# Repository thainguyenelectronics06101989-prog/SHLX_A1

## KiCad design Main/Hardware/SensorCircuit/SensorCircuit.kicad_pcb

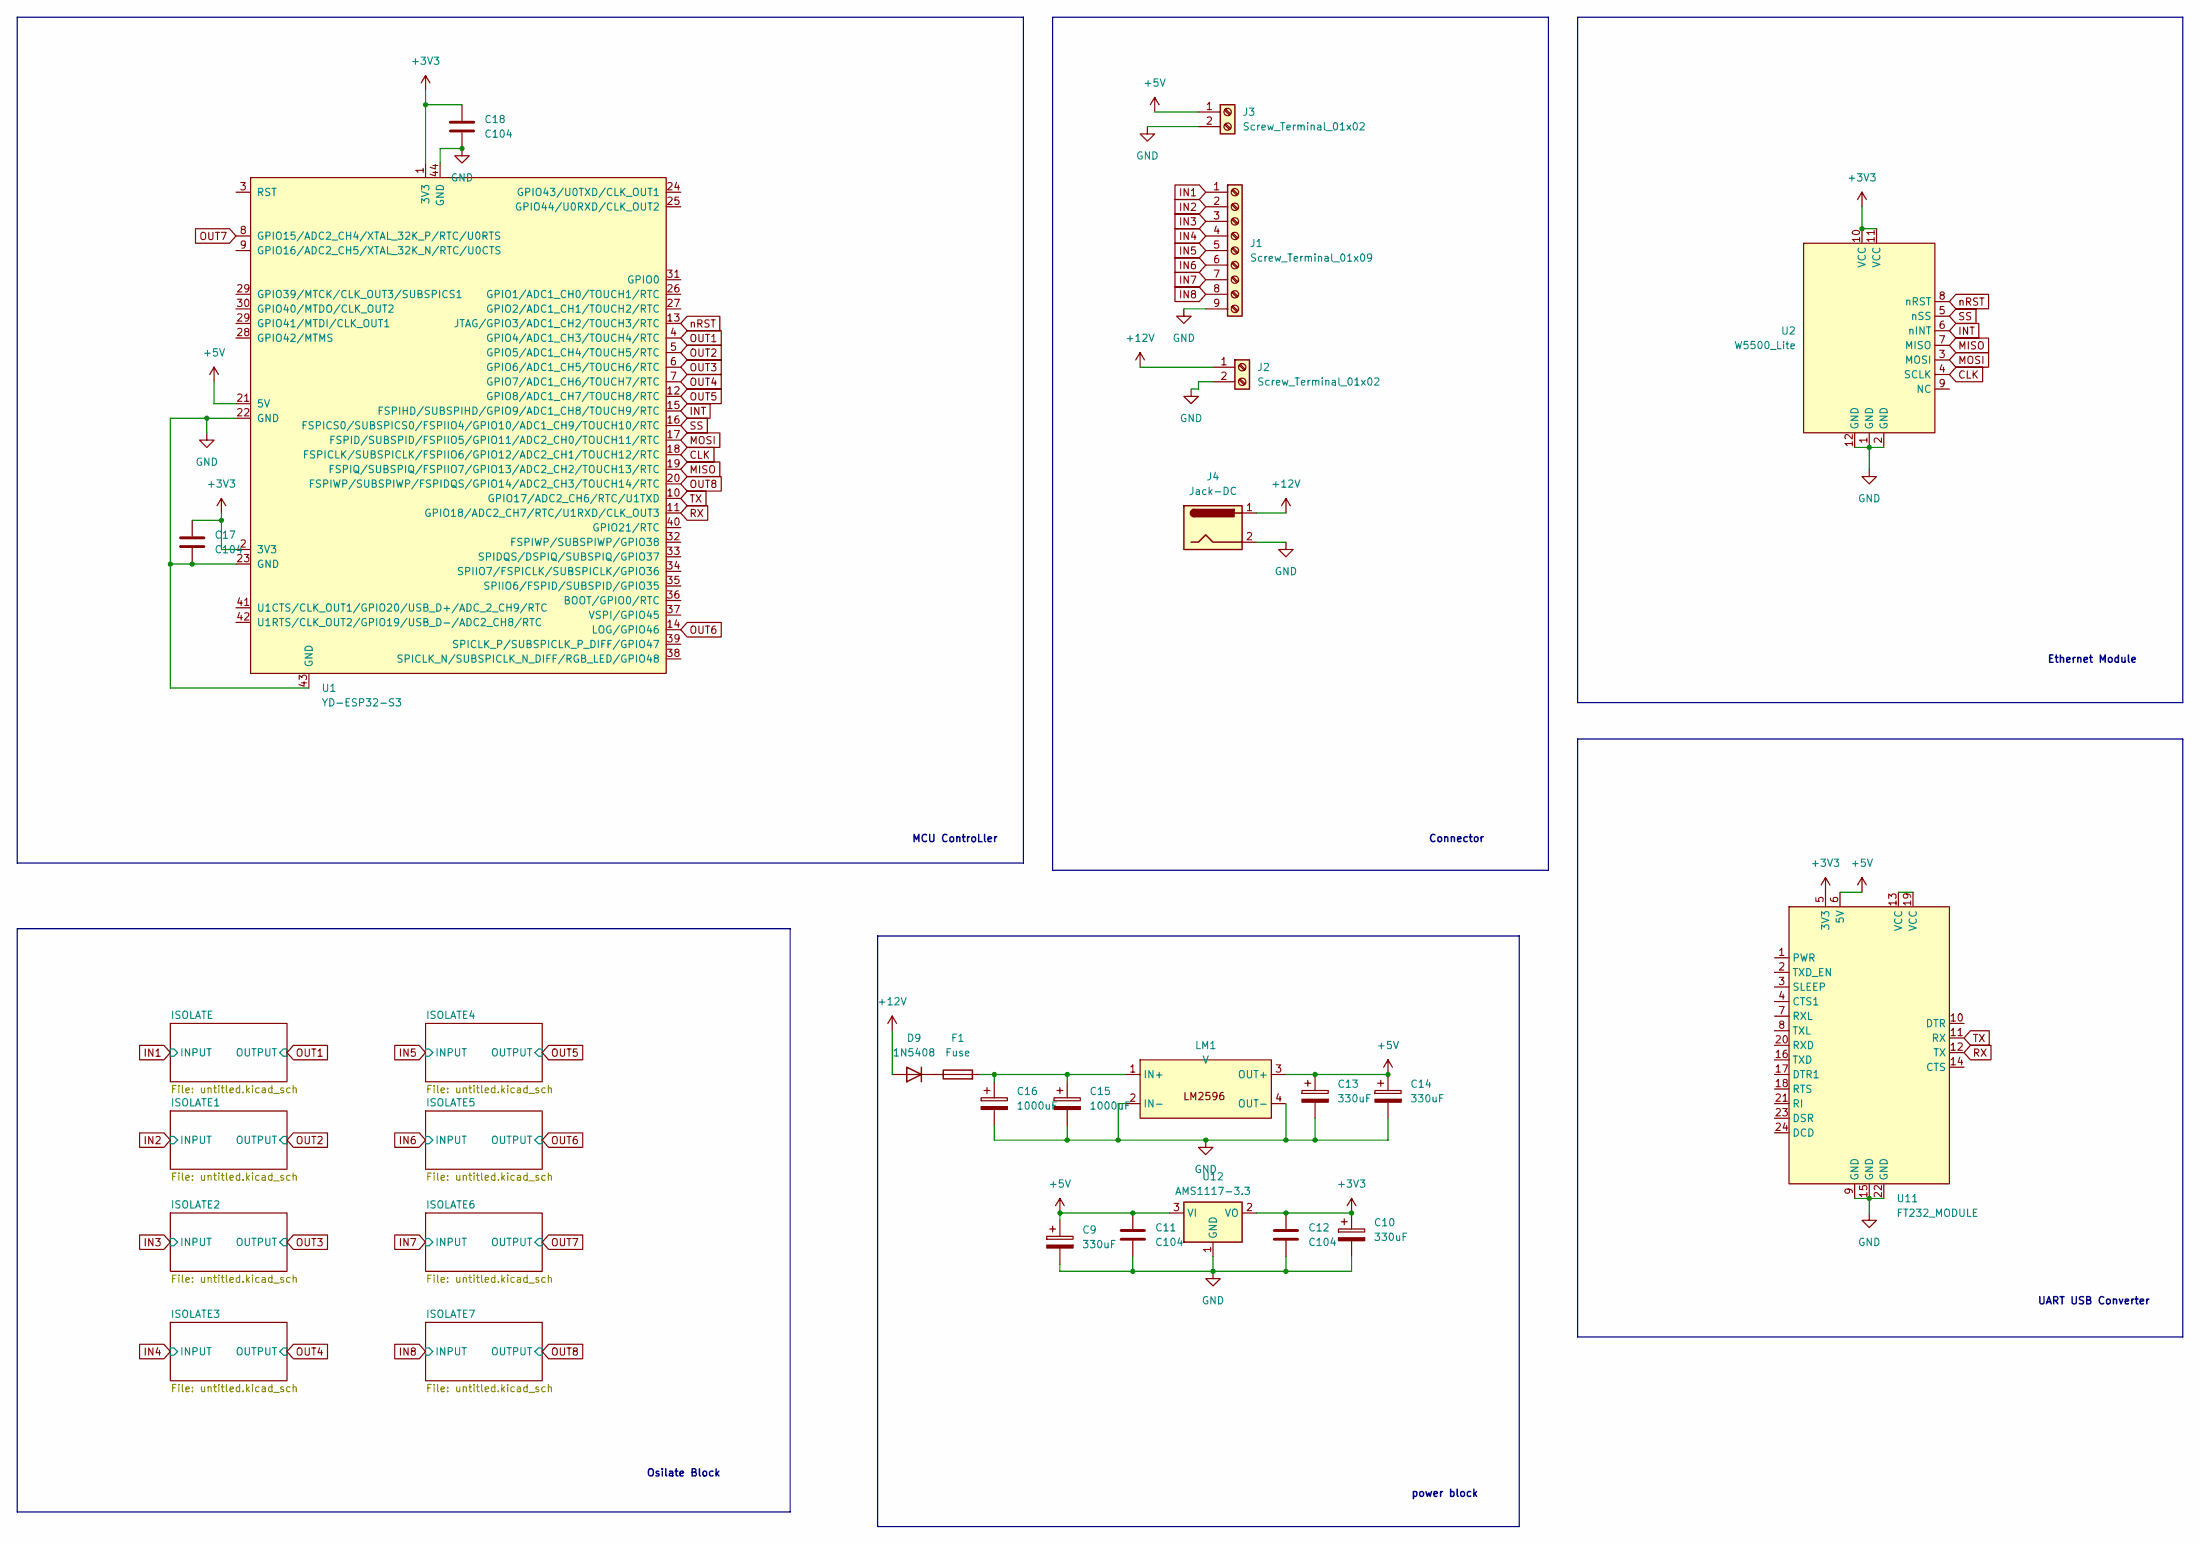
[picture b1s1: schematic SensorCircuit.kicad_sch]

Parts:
C9, C10, C13, C14: 330uF; C_Radial_D8.0mm_H7.0mm_P3.50mm
C11, C12, C17, C18: C104; C_Disc_D5.0mm_W2.5mm_P5.00mm
C15, C16: 1000uF; C_Radial_D10.0mm_H12.5mm_P5.00mm
D9: 1N5408; D_DO-201AD_P15.24mm_Horizontal
F1: Fuse; Fuseholder_Clip-5x20mm_Schurter_OG_Lateral_P15.00x5.00mm_D1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
J1: Screw_Terminal_01x09; TerminalBlock_Phoenix_MKDS-1,5-9-5.08_1x09_P5.08mm_Horizont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
J2, J3: Screw_Terminal_01x02; TerminalBlock_Phoenix_MKDS-1,5-2-5.08_1x02_P5.08mm_Horizont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
J4: Jack-DC; BarrelJack_GCT_DCJ200-10-A_Horizontal
LM1: V; LM2596_Module
U1: YD-ESP32-S3
U2: W5500_Lite; W5500_Lite_module
U11: FT232_MODULE; FT232_Module
U12: AMS1117-3.3; SOT-223-3_TabPin2

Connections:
+3V3: C10.1, C12.1, C17.1, C18.1, U1.1 (3V3), U1.2 (3V3), U2.10 (VCC), U2.11 (VCC), U11.5 (3V3), U12.2 (VO); also elsewhere on the board
+5V: C9.1, C11.1, C13.1, C14.1, J3.1, LM1.3 (OUT+), U1.21 (5V), U11.6 (5V), U12.3 (VI)
+12V: D9.2 (A), J2.1, J4.1; also elsewhere on the board
CLK: U1.18 (FSPICLK/SUBSPICLK/FSPIIO6/GPIO12/ADC2_C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), U2.4 (SCLK)
GND: C9.2, C10.2, C11.2, C12.2, C13.2, C14.2, C15.2, C16.2, C17.2, C18.2, J1.9, J2.2, J3.2, J4.2, LM1.2 (IN-), LM1.4 (OUT-), U1.22 (GND), U1.23 (GND), U1.43 (GND), U1.44 (GND), U2.1 (GND), U2.2 (GND), U2.12 (GND), U11.9 (GND), U11.15 (GND), U11.22 (GND), U12.1 (GND); also elsewhere on the board
IN1: J1.1; also elsewhere on the board
IN2: J1.2; also elsewhere on the board
IN3: J1.3; also elsewhere on the board
IN4: J1.4; also elsewhere on the board
IN5: J1.5; also elsewhere on the board
IN6: J1.6; also elsewhere on the board
IN7: J1.7; also elsewhere on the board
IN8: J1.8; also elsewhere on the board
INT: U1.15 (FSPIHD/SUBSPIHD/GPIO9/ADC1_CH8/TOUCH9/R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), U2.6 (nINT)
MISO: U1.19 (FSPIQ/SUBSPIQ/FSPIIO7/GPIO13/ADC2_CH2/T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), U2.7 (MISO)
MOSI: U1.17 (FSPID/SUBSPID/FSPIIO5/GPIO11/ADC2_CH0/T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), U2.3 (MOSI)
unnamed: D9.1 (K), F1.1
unnamed: C15.1, C16.1, F1.2, LM1.1 (IN+)
unnamed: U11.13 (VCC), U11.19 (VCC)
OUT1: U1.4 (GPIO4/ADC1_CH3/TOUCH4/RTC); also elsewhere on the board
OUT2: U1.5 (GPIO5/ADC1_CH4/TOUCH5/RTC); also elsewhere on the board
OUT3: U1.6 (GPIO6/ADC1_CH5/TOUCH6/RTC); also elsewhere on the board
OUT4: U1.7 (GPIO7/ADC1_CH6/TOUCH7/RTC); also elsewhere on the board
OUT5: U1.12 (GPIO8/ADC1_CH7/TOUCH8/RTC); also elsewhere on the board
OUT6: U1.14 (LOG/GPIO46); also elsewhere on the board
OUT7: U1.8 (GPIO15/ADC2_CH4/XTAL_32K_P/RTC/U0RTS); also elsewhere on the board
OUT8: U1.20 (FSPIWP/SUBSPIWP/FSPIDQS/GPIO14/ADC2_CH3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); also elsewhere on the board
RX: U1.11 (GPIO18/ADC2_CH7/RTC/U1RXD/CLK_OUT3), U11.12 (TX)
SS: U1.16 (FSPICS0/SUBSPICS0/FSPIIO4/GPIO10/ADC1_C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), U2.5 (nSS)
TX: U1.10 (GPIO17/ADC2_CH6/RTC/U1TXD), U11.11 (RX)
nRST: U1.13 (JTAG/GPIO3/ADC1_CH2/TOUCH3/RTC), U2.8 (nRST)

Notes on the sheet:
Ethernet Module
UART USB Converter
Osilate Block
Connector
MCU ControLler
power block

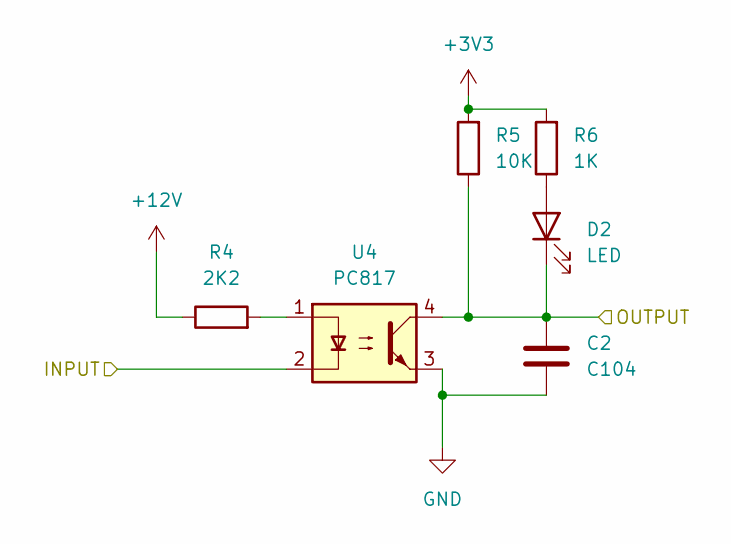
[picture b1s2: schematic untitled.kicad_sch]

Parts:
C2: C104; C_Disc_D5.0mm_W2.5mm_P5.00mm
D2: LED; LED_D3.0mm
R4: 2K2; R_Axial_DIN0207_L6.3mm_D2.5mm_P7.62mm_Horizontal
R5: 10K; R_Axial_DIN0207_L6.3mm_D2.5mm_P7.62mm_Horizontal
R6: 1K; R_Axial_DIN0207_L6.3mm_D2.5mm_P7.62mm_Horizontal
U4: PC817; DIP-4_W7.62mm

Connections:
+3V3: R5.2, R6.2; also elsewhere on the board
+12V: R4.1; also elsewhere on the board
GND: C2.2, U4.3; also elsewhere on the board
IN1: U4.2; also elsewhere on the board
unnamed: D2.2 (A), R6.1
unnamed: R4.2, U4.1
OUT1: C2.1, D2.1 (K), R5.1, U4.4; also elsewhere on the board

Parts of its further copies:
C1, C3, C4, C5, C6, C7, C8: C104; C_Disc_D5.0mm_W2.5mm_P5.00mm
D1, D3, D4, D5, D6, D7, D8: LED; LED_D3.0mm
R1, R7, R10, R13, R16, R19, R22: 2K2; R_Axial_DIN0207_L6.3mm_D2.5mm_P7.62mm_Horizontal
R2, R8, R11, R14, R17, R20, R23: 10K; R_Axial_DIN0207_L6.3mm_D2.5mm_P7.62mm_Horizontal
R3, R9, R12, R15, R18, R21, R24: 1K; R_Axial_DIN0207_L6.3mm_D2.5mm_P7.62mm_Horizontal
U3, U5, U6, U7, U8, U9, U10: PC817; DIP-4_W7.62mm

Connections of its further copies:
+3V3: R2.2, R3.2, R8.2, R9.2, R11.2, R12.2, R14.2, R15.2, R17.2, R18.2, R20.2, R21.2, R23.2, R24.2; also elsewhere on the board
+12V: R1.1, R7.1, R10.1, R13.1, R16.1, R19.1, R22.1; also elsewhere on the board
GND: C1.2, C3.2, C4.2, C5.2, C6.2, C7.2, C8.2, U3.3, U5.3, U6.3, U7.3, U8.3, U9.3, U10.3; also elsewhere on the board
IN2: U3.2; also elsewhere on the board
IN3: U5.2; also elsewhere on the board
IN4: U6.2; also elsewhere on the board
IN5: U7.2; also elsewhere on the board
IN6: U8.2; also elsewhere on the board
IN7: U9.2; also elsewhere on the board
IN8: U10.2; also elsewhere on the board
unnamed: D1.2 (A), R3.1
unnamed: D3.2 (A), R9.1
unnamed: D4.2 (A), R12.1
unnamed: D5.2 (A), R15.1
unnamed: D6.2 (A), R18.1
unnamed: D7.2 (A), R21.1
unnamed: D8.2 (A), R24.1
unnamed: R1.2, U3.1
unnamed: R7.2, U5.1
unnamed: R10.2, U6.1
unnamed: R13.2, U7.1
unnamed: R16.2, U8.1
unnamed: R19.2, U9.1
unnamed: R22.2, U10.1
OUT2: C1.1, D1.1 (K), R2.1, U3.4; also elsewhere on the board
OUT3: C3.1, D3.1 (K), R8.1, U5.4; also elsewhere on the board
OUT4: C4.1, D4.1 (K), R11.1, U6.4; also elsewhere on the board
OUT5: C5.1, D5.1 (K), R14.1, U7.4; also elsewhere on the board
OUT6: C6.1, D6.1 (K), R17.1, U8.4; also elsewhere on the board
OUT7: C7.1, D7.1 (K), R20.1, U9.4; also elsewhere on the board
OUT8: C8.1, D8.1 (K), R23.1, U10.4; also elsewhere on the board

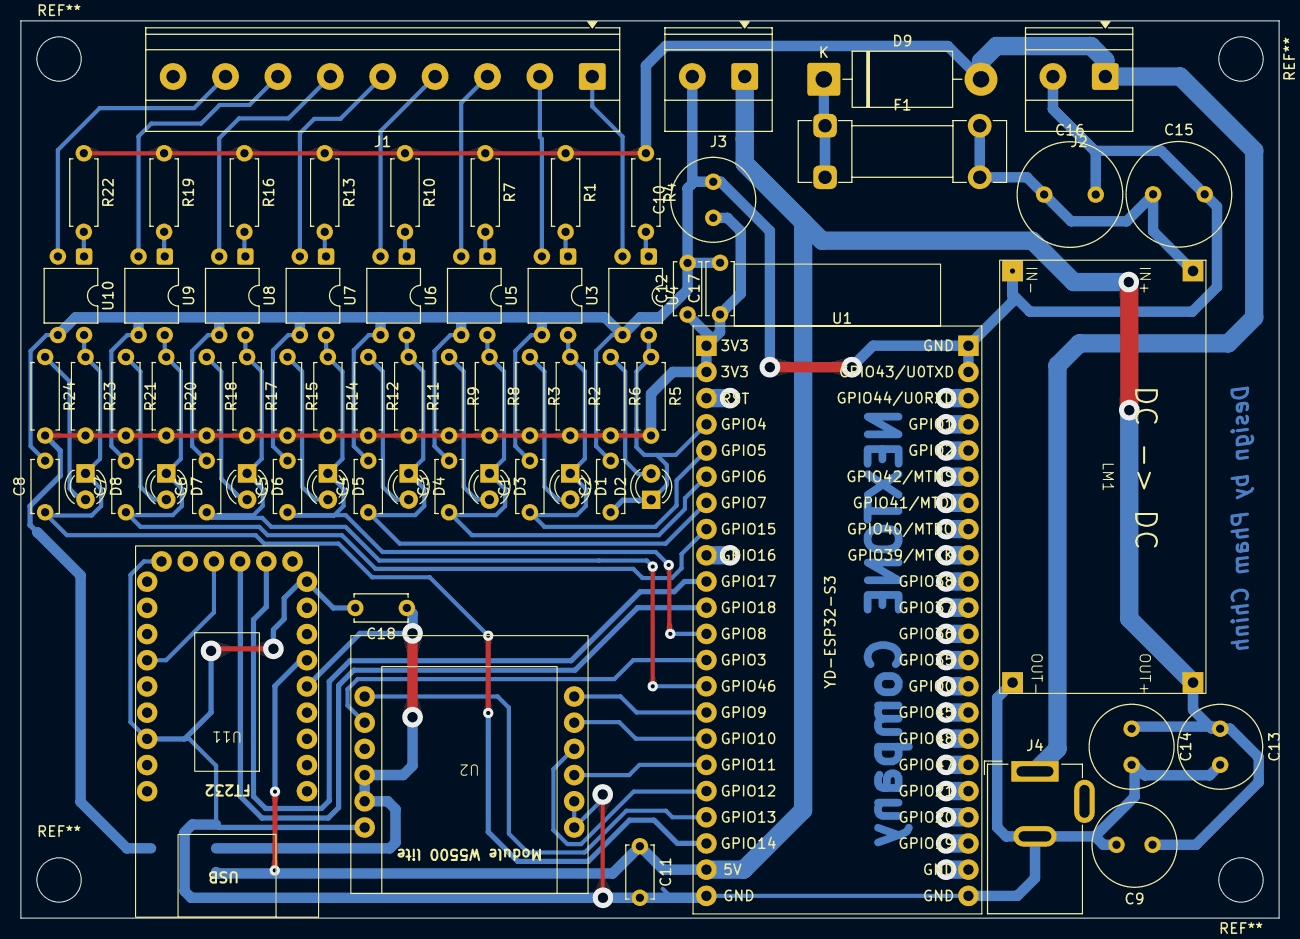
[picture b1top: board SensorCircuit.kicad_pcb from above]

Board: 2 copper layers, 122.0 x 87.0 mm, 69 parts (1 on the bottom side), 47 nets.

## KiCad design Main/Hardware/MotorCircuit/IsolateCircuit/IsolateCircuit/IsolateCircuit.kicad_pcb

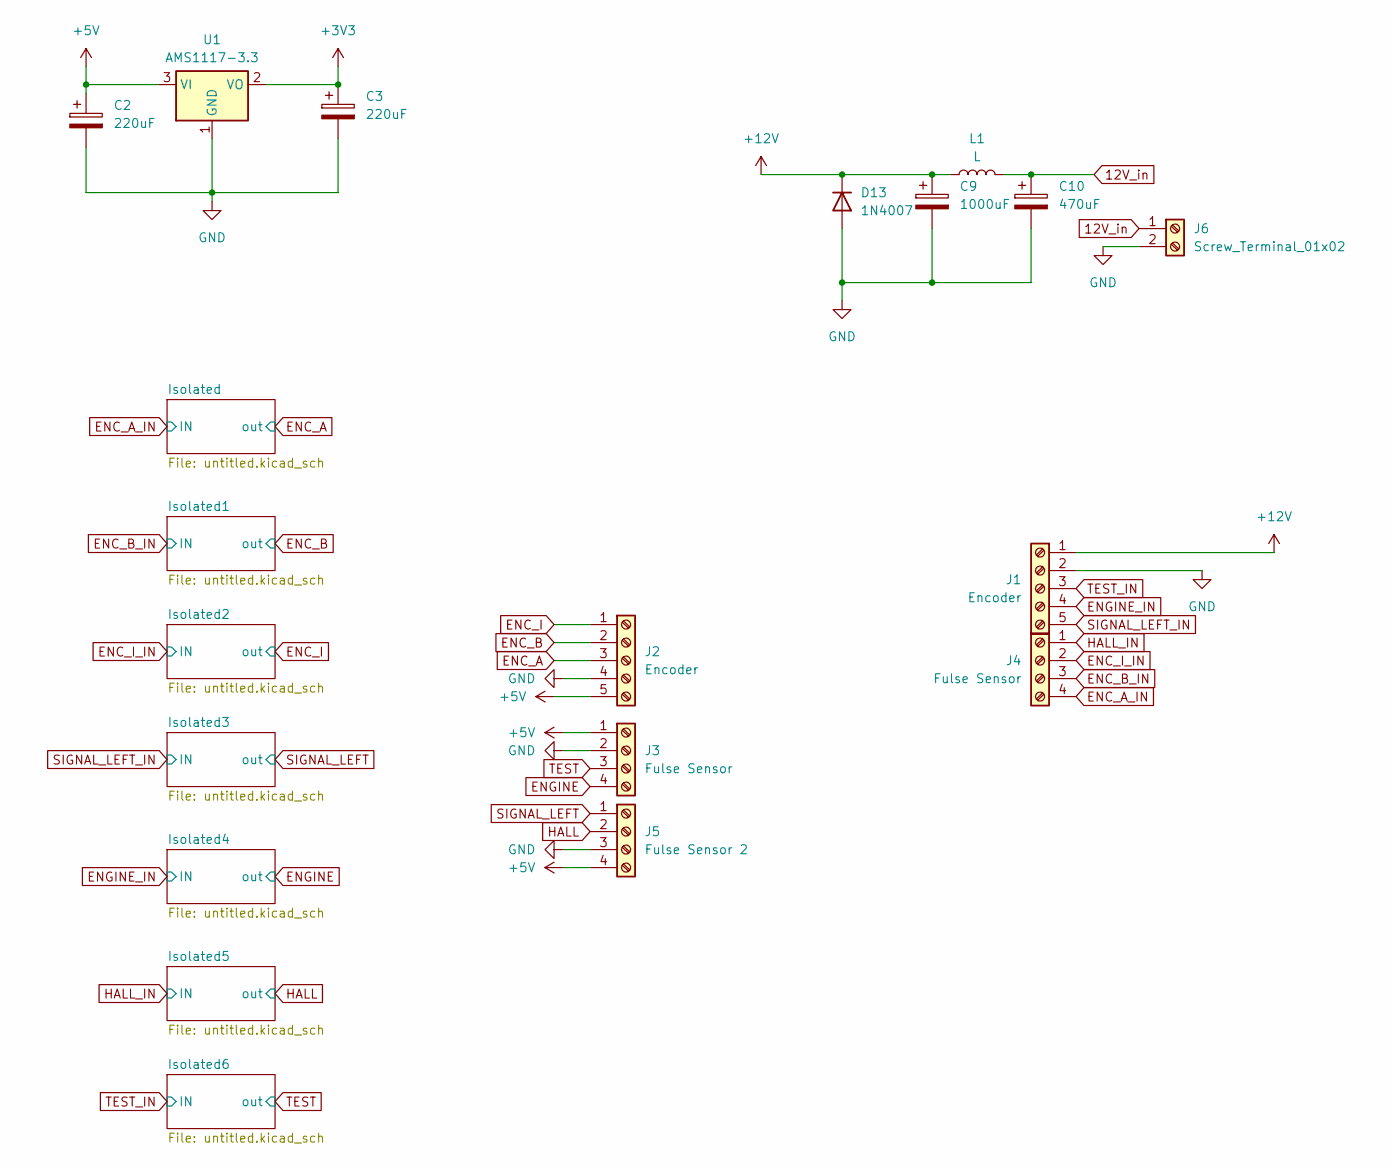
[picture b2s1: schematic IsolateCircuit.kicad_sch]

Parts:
C2, C3: 220uF; CP_Radial_D6.3mm_P2.50mm
C9: 1000uF; CP_Radial_D8.0mm_P2.50mm
C10: 470uF; CP_Radial_D8.0mm_P2.50mm
D13: 1N4007; D_DO-41_SOD81_P10.16mm_Horizontal
J1, J2: Encoder; TerminalBlock_Phoenix_MKDS-1,5-5-5.08_1x05_P5.08mm_Horizont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
J3, J4: Fulse Sensor; TerminalBlock_Phoenix_MKDS-1,5-4_1x04_P5.00mm_Horizontal
J5: Fulse Sensor 2; TerminalBlock_Phoenix_MKDS-1,5-4_1x04_P5.00mm_Horizontal
J6: Screw_Terminal_01x02; TerminalBlock_Phoenix_MKDS-1,5-2-5.08_1x02_P5.08mm_Horizont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
L1: L; L_Toroid_Vertical_L14.0mm_W5.6mm_P5.30mm_Bourns_5700
U1: AMS1117-3.3; SOT-223-3_TabPin2

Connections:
12V_in: C10.1, J6.1, L1.2
+3V3: C3.1, U1.2 (VO); also elsewhere on the board
+5V: C2.1, J2.5, J3.1, J5.4, U1.3 (VI)
+12V: C9.1, D13.1 (K), J1.1, L1.1; also elsewhere on the board
ENC_A: J2.3; also elsewhere on the board
ENC_A_IN: J4.4; also elsewhere on the board
ENC_B: J2.2; also elsewhere on the board
ENC_B_IN: J4.3; also elsewhere on the board
ENC_I: J2.1; also elsewhere on the board
ENC_I_IN: J4.2; also elsewhere on the board
ENGINE: J3.4; also elsewhere on the board
ENGINE_IN: J1.4; also elsewhere on the board
GND: C2.2, C3.2, C9.2, C10.2, D13.2 (A), J1.2, J2.4, J3.2, J5.3, J6.2, U1.1 (GND); also elsewhere on the board
HALL: J5.2; also elsewhere on the board
HALL_IN: J4.1; also elsewhere on the board
SIGNAL_LEFT: J5.1; also elsewhere on the board
SIGNAL_LEFT_IN: J1.5; also elsewhere on the board
TEST: J3.3; also elsewhere on the board
TEST_IN: J1.3; also elsewhere on the board

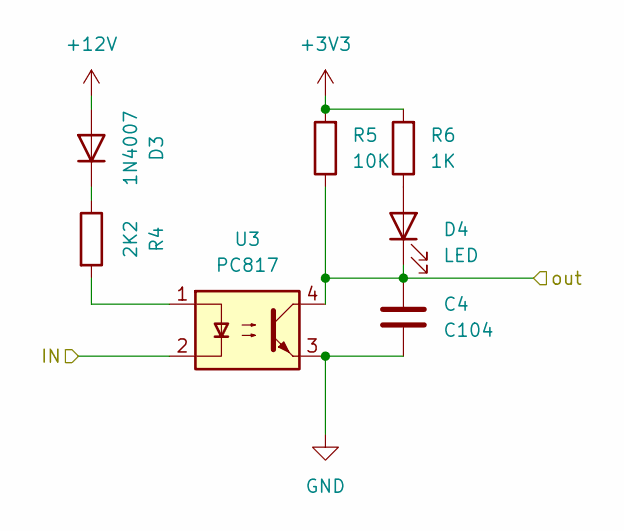
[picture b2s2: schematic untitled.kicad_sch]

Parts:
C4: C104; C_Disc_D5.1mm_W3.2mm_P5.00mm
D3: 1N4007; D_DO-41_SOD81_P10.16mm_Horizontal
D4: LED; LED_D3.0mm
R4: 2K2; R_Axial_DIN0207_L6.3mm_D2.5mm_P10.16mm_Horizontal
R5: 10K; R_Axial_DIN0207_L6.3mm_D2.5mm_P10.16mm_Horizontal
R6: 1K; R_Axial_DIN0207_L6.3mm_D2.5mm_P10.16mm_Horizontal
U3: PC817; DIP-4_W7.62mm

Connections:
+3V3: R5.2, R6.2; also elsewhere on the board
+12V: D3.2 (A); also elsewhere on the board
ENC_A: C4.1, D4.1 (K), R5.1, U3.4; also elsewhere on the board
ENC_A_IN: U3.2; also elsewhere on the board
GND: C4.2, U3.3; also elsewhere on the board
unnamed: D3.1 (K), R4.1
unnamed: D4.2 (A), R6.1
unnamed: R4.2, U3.1

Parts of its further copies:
C1, C5, C6, C7, C8, C11: C104; C_Disc_D5.1mm_W3.2mm_P5.00mm
D1, D5, D7, D9, D11, D14: 1N4007; D_DO-41_SOD81_P10.16mm_Horizontal
D2, D6, D8, D10, D12, D15: LED; LED_D3.0mm
R1, R7, R10, R13, R16, R19: 2K2; R_Axial_DIN0207_L6.3mm_D2.5mm_P10.16mm_Horizontal
R2, R8, R11, R14, R17, R20: 10K; R_Axial_DIN0207_L6.3mm_D2.5mm_P10.16mm_Horizontal
R3, R9, R12, R15, R18, R21: 1K; R_Axial_DIN0207_L6.3mm_D2.5mm_P10.16mm_Horizontal
U2, U4, U5, U6, U7, U8: PC817; DIP-4_W7.62mm

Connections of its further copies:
+3V3: R2.2, R3.2, R8.2, R9.2, R11.2, R12.2, R14.2, R15.2, R17.2, R18.2, R20.2, R21.2; also elsewhere on the board
+12V: D1.2 (A), D5.2 (A), D7.2 (A), D9.2 (A), D11.2 (A), D14.2 (A); also elsewhere on the board
ENC_B: C1.1, D2.1 (K), R2.1, U2.4; also elsewhere on the board
ENC_B_IN: U2.2; also elsewhere on the board
ENC_I: C5.1, D6.1 (K), R8.1, U4.4; also elsewhere on the board
ENC_I_IN: U4.2; also elsewhere on the board
ENGINE: C7.1, D10.1 (K), R14.1, U6.4; also elsewhere on the board
ENGINE_IN: U6.2; also elsewhere on the board
GND: C1.2, C5.2, C6.2, C7.2, C8.2, C11.2, U2.3, U4.3, U5.3, U6.3, U7.3, U8.3; also elsewhere on the board
HALL: C8.1, D12.1 (K), R17.1, U7.4; also elsewhere on the board
HALL_IN: U7.2; also elsewhere on the board
unnamed: D1.1 (K), R1.1
unnamed: D2.2 (A), R3.1
unnamed: D5.1 (K), R7.1
unnamed: D6.2 (A), R9.1
unnamed: D7.1 (K), R10.1
unnamed: D8.2 (A), R12.1
unnamed: D9.1 (K), R13.1
unnamed: D10.2 (A), R15.1
unnamed: D11.1 (K), R16.1
unnamed: D12.2 (A), R18.1
unnamed: D14.1 (K), R19.1
unnamed: D15.2 (A), R21.1
unnamed: R1.2, U2.1
unnamed: R7.2, U4.1
unnamed: R10.2, U5.1
unnamed: R13.2, U6.1
unnamed: R16.2, U7.1
unnamed: R19.2, U8.1
SIGNAL_LEFT: C6.1, D8.1 (K), R11.1, U5.4; also elsewhere on the board
SIGNAL_LEFT_IN: U5.2; also elsewhere on the board
TEST: C11.1, D15.1 (K), R20.1, U8.4; also elsewhere on the board
TEST_IN: U8.2; also elsewhere on the board

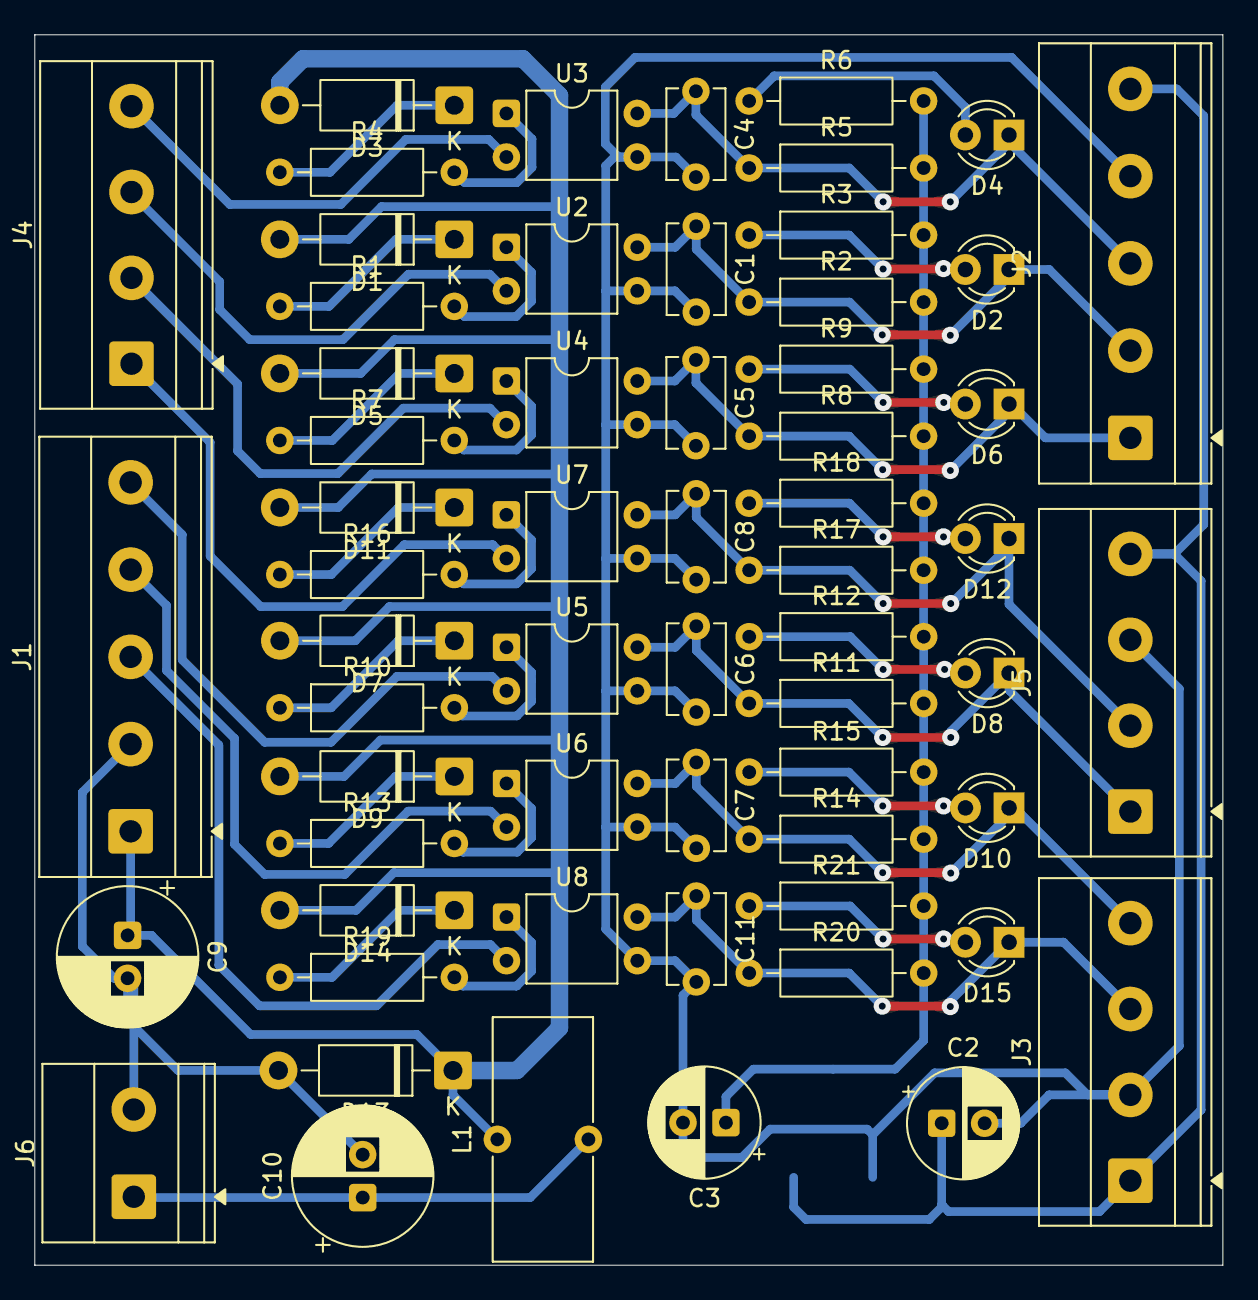
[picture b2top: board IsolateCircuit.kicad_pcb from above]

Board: 2 copper layers, 69.2 x 71.7 mm, 62 parts (1 on the bottom side), 40 nets.

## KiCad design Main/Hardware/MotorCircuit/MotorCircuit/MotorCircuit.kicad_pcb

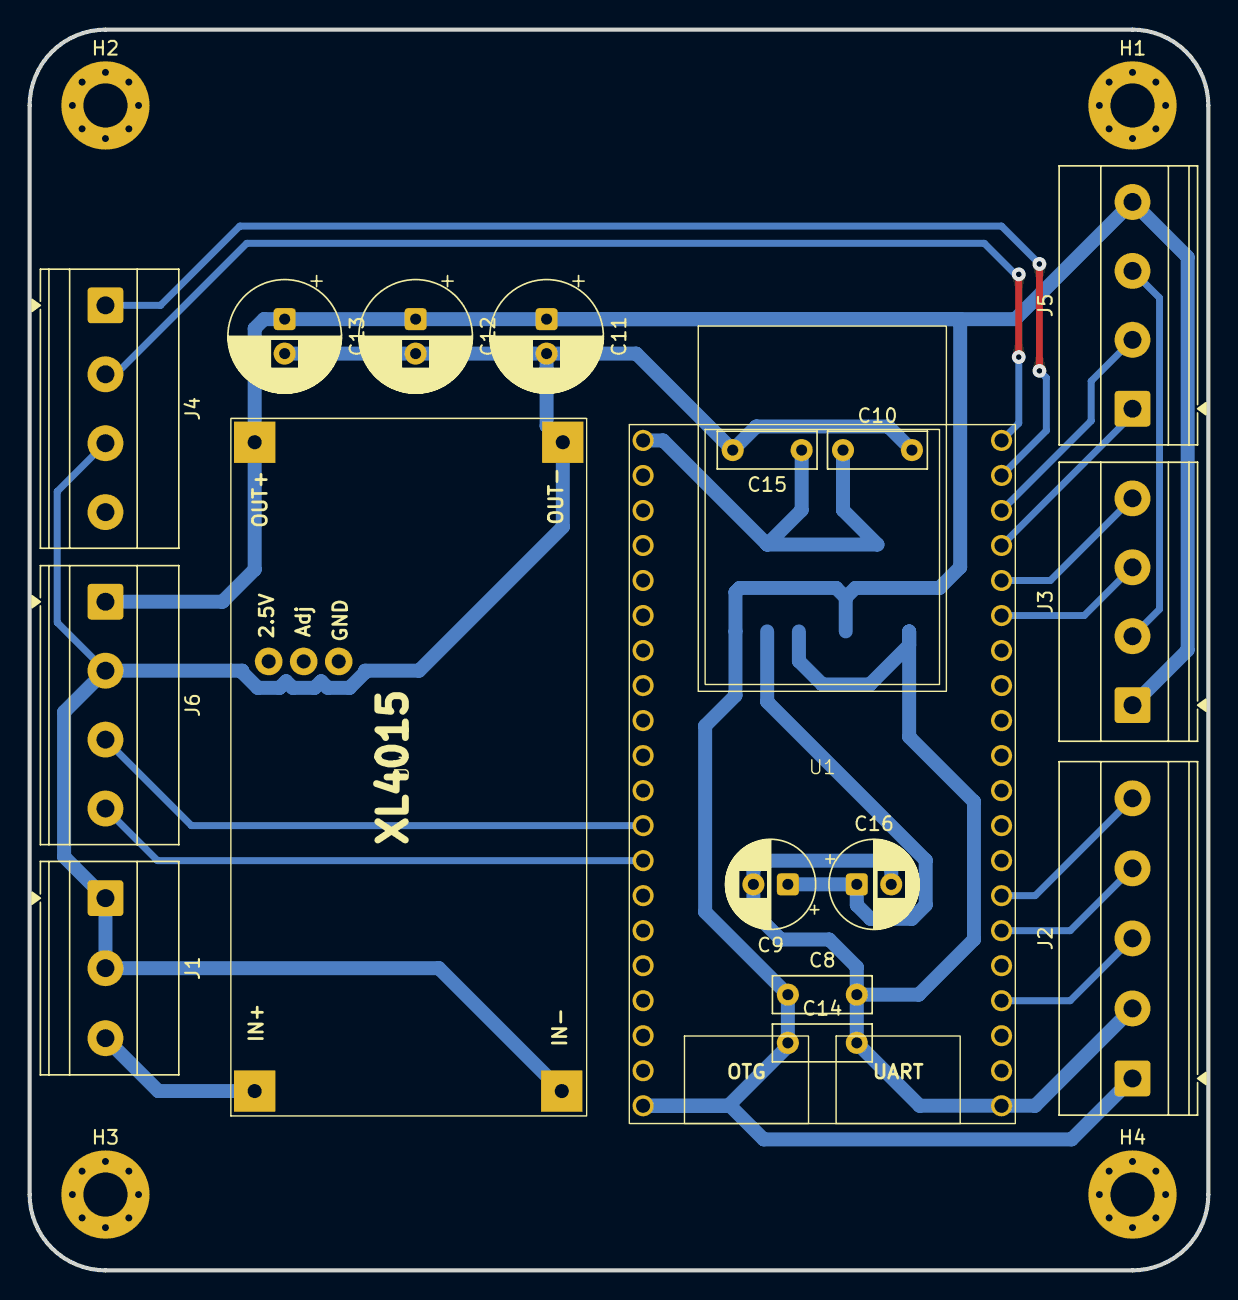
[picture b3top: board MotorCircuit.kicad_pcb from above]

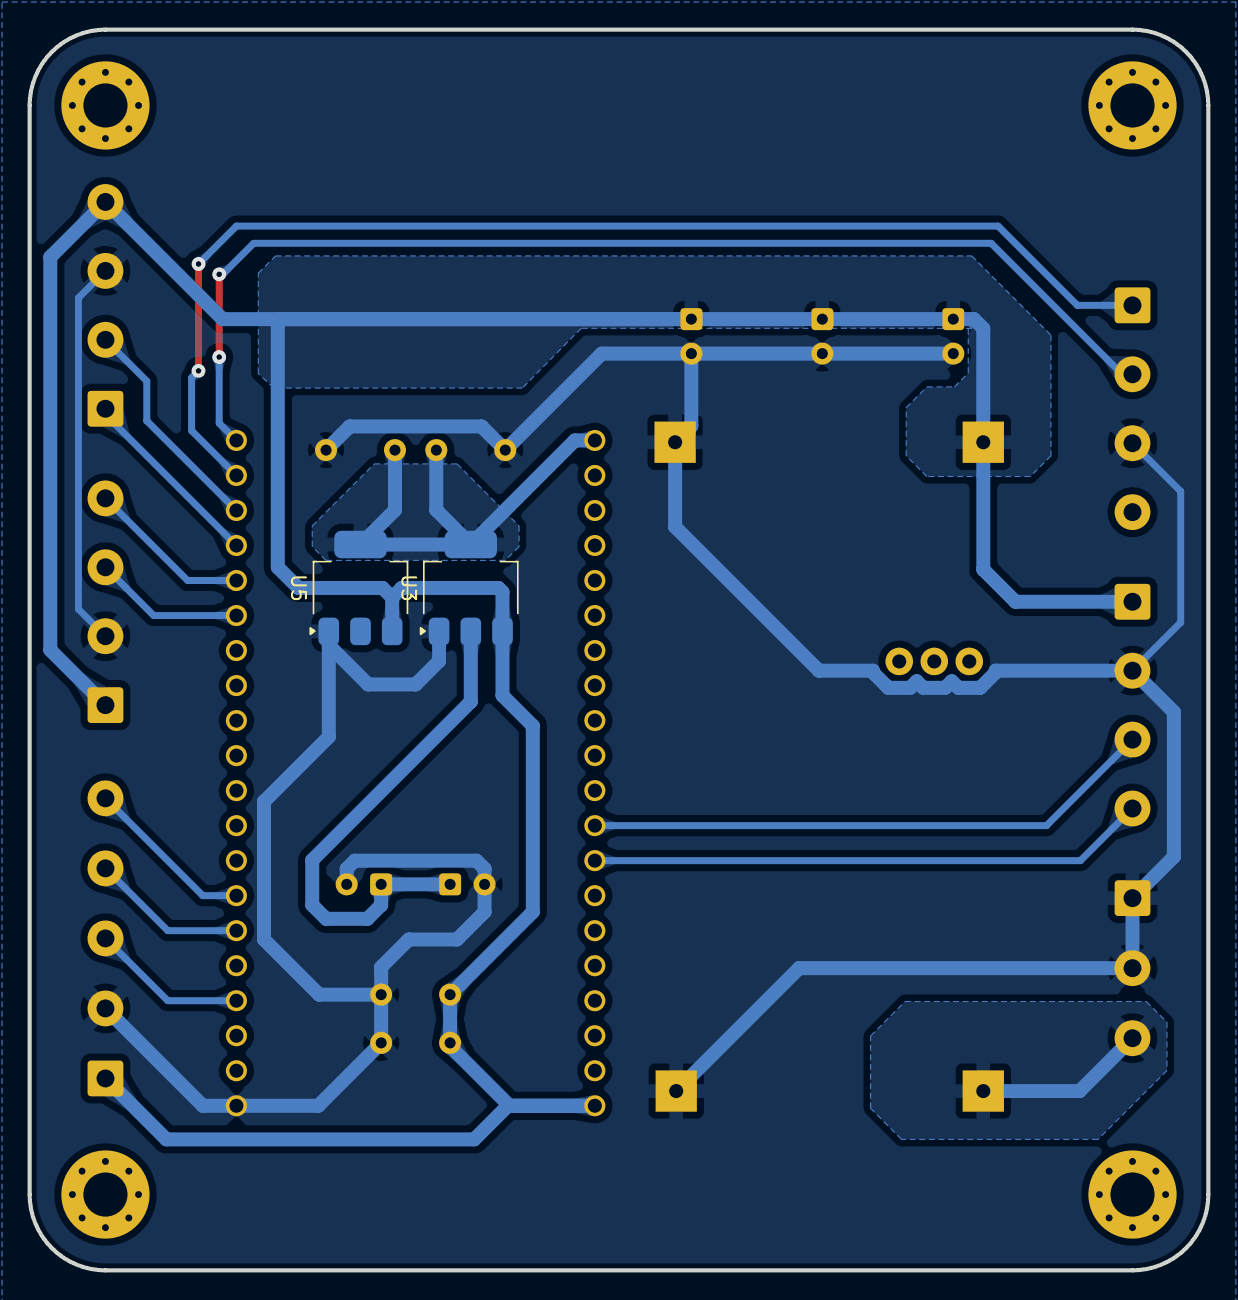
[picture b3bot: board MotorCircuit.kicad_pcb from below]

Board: 2 copper layers, 85.5 x 90.0 mm, 23 parts (2 on the bottom side), 15 nets.

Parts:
C8, C10, C14, C15: C104; C_Disc_D7.0mm_W2.5mm_P5.00mm
C9, C16: 100uF; CP_Radial_D6.3mm_P2.50mm
C11, C12, C13: 330uF; CP_Radial_D8.0mm_P2.50mm
H1, H2, H3, H4: MountingHole; MountingHole_3.2mm_M3_Pad_Via
J1: DC IN; TerminalBlock_Phoenix_MKDS-1,5-3-5.08_1x03_P5.08mm_Horizont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
J2: Encoder; TerminalBlock_Phoenix_MKDS-1,5-5-5.08_1x05_P5.08mm_Horizont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
J3: Fulse Sensor; TerminalBlock_Phoenix_MKDS-1,5-4_1x04_P5.00mm_Horizontal
J4: Uart; TerminalBlock_Phoenix_MKDS-1,5-4_1x04_P5.00mm_Horizontal
J5: Fulse Sensor 2; TerminalBlock_Phoenix_MKDS-1,5-4_1x04_P5.00mm_Horizontal
J6: Fulse Sensor 3; TerminalBlock_Phoenix_MKDS-1,5-4_1x04_P5.00mm_Horizontal
U1: ESP32-S3-CAM
U3, U5: AMS1117-3.3; SOT-223-3_TabPin2
U4: XL4015_Module(CC-CV); XL4015_CVCC_Module

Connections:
+3.3V: C9.1, C10.1, C15.1, C16.1, J4.4, U1.J1_2 (3V3), U3.2 (VO), U5.2 (VO)
+5V: C8.1, C11.1, C12.1, C13.1, C14.1, J2.1, J3.1, J5.4, J6.1, U1.J1_21 (5V0), U3.3 (VI), U4.3 (VOUT+), U5.3 (VI)
+15V: J1.3, U4.1 (VIN+)
ENC_A: J2.3, U1.J3_18 (GPIO21)
ENC_B: J2.4, U1.J3_16 (GPIO48)
ENC_I: J2.5, U1.J3_15 (GPIO45)
GND: C8.2, C9.2, C10.2, C11.2, C12.2, C13.2, C14.2, C15.2, C16.2, J1.1, J1.2, J2.2, J3.2, J4.3, J5.3, J6.2, U1.J3_21 (GND), U3.1 (GND), U4.2 (VIN-), U4.4 (VOUT-), U5.1 (GND)
RX0: J4.1, U1.J3_3 (U0RXD/GPIO44)
TX0: J4.2, U1.J3_2 (U0TXD/GPIO43)
X1_IN: J3.3, U1.J3_7 (MTDI/GPIO41)
X2_IN: J3.4, U1.J3_6 (MTMS/GPIO42)
X3_IN: J5.1, U1.J3_5 (GPIO2)
X4_IN: J5.2, U1.J3_4 (GPIO1)
X5_IN: J6.3, U1.J1_13 (GPIO3)
X6_IN: J6.4, U1.J1_14 (GPIO46)

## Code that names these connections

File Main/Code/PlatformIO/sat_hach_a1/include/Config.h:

#ifndef CONFIG_H
#define CONFIG_H

#define X1_IN 41
#define X2_IN 42
#define X3_IN 2
#define X4_IN 1
#define X5_IN 3
#define X6_IN 46
#define X_IN 47

#define ENC_A 21
#define ENC_B 48
#define ENC_I 45

#endif

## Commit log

2025-10-13 update platformIO
2025-11-06 update code
